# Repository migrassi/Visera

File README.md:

# Visera HX-8K – (HX-8K Visor Hat)
#### Versión 1.0  - Quarantine edition
Extensión I/O para la iCE40HX-8K Breakout Board Evaluation Kit de Lattice 

## Descripción 

La Visera es un accesorio de conexión directa a la placa de entrenamiento en tecnología FPGA “iCE40HX-8K Breakout Board” de Lattice Semiconductors, un modelo basado en la conocida familia FPGA iCE40, de esa marca. La placa se inserta directamente en el único conector de 40 pines que viene poblado de fabrica en la Breakout Board, quedando “en voladizo” hacia afuera, dejando los otros tres conectores de 40 pines, jumpers, LEDs y demás partes de la placa original completamente descubiertos y libres para otras aplicaciones. Esta disposición flotante, sujeta sólo por un lado, es la que le da el nombre de Visera o Visor Hat. 

La Visera fue desarrollada en Mayo de 2020, en el marco de la pandemia mundial del COVID19 y particularmente la cuarentena estricta de la Ciudad de Buenos Aires. Fue resuelta, por lo tanto, con el material del cajón de rezagos del autor, dadas las dificultades  para adquirir componentes nuevos. Esta importante restricción de diseño constituye una de sus fortalezas, ya que prácticamente cualquier aficionado o profesional de la electrónica tendrá disponibles esos mismos componente en su propio cajón, o los podrá adquirir con facilidad en negocios de cercanías.

## Enlaces

Website:https://miguelgrassi.com.ar/visera/

Video de ejemplo. Encoder rotativo, contador en Hexa y decimal, con display de dos dígitos: https://youtu.be/07v77fjeGq4 

Herramienta para generación de caracteres y símbolos personalizados para usar en el display Matriz de Leds: https://editor.p5js.org/migrassi/present/nZ4poi31X

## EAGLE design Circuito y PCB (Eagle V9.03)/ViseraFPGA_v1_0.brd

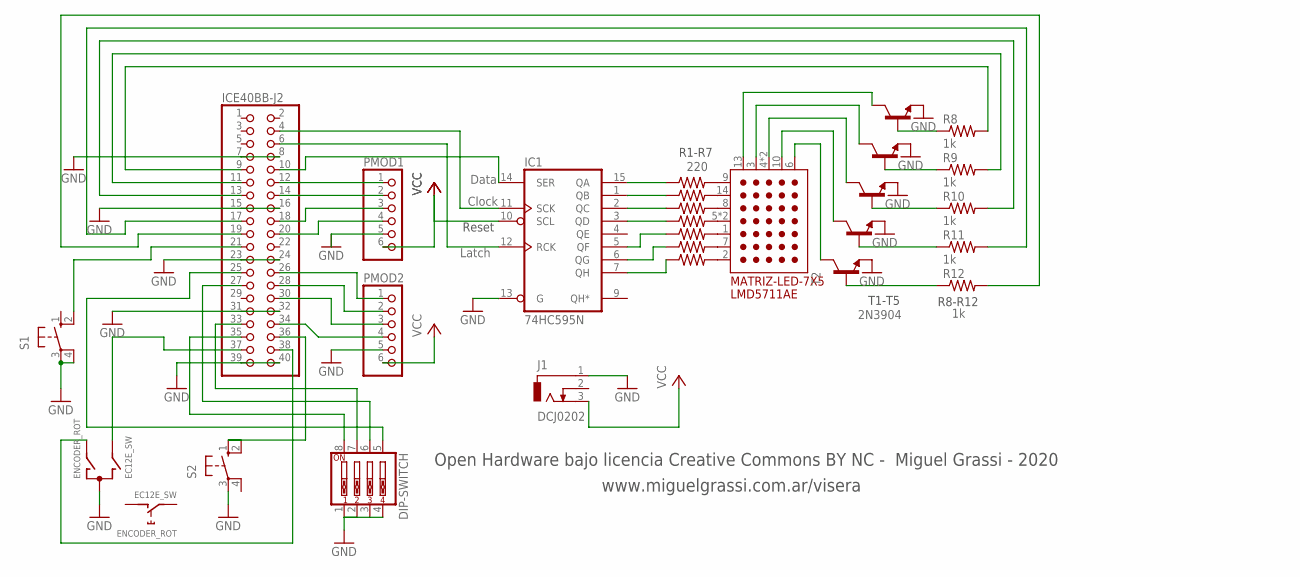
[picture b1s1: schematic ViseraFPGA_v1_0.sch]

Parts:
DIP-SWITCH: SW_DIP-4; EDG-04
ENCODER_ROT: EC12E_SW; ALPS_EC12E_SW
IC1: 74HC595N; DIL16
ICE40BB-J2: PINHD-2X20; 2X20
J1: DCJ0202
MATRIZ-LED-7X5: LMD5711AE
PMOD1, PMOD2: PINHD-1X6; 1X06
R1, R2, R3, R4, R5, R6, R7: 220; 0207/7
R8, R9, R10, R11, R12: 1k; 0207/7
S1, S2: 10-XX; B3F-10XX
T1, T2, T3, T4, T5: 2N3904; TO92

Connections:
GND: DIP-SWITCH.1, DIP-SWITCH.2, DIP-SWITCH.3, DIP-SWITCH.4, ENCODER_ROT.C, IC1.8 (GND), IC1.13 (G), ICE40BB-J2.7, ICE40BB-J2.8, ICE40BB-J2.15, ICE40BB-J2.16, ICE40BB-J2.23, ICE40BB-J2.24, ICE40BB-J2.31, ICE40BB-J2.32, ICE40BB-J2.39, ICE40BB-J2.40, J1.1, PMOD1.5, PMOD2.5, S1.3, S1.4 (P1), S2.3, T1.3 (E), T2.3 (E), T3.3 (E), T4.3 (E), T5.3 (E)
unnamed: MATRIZ-LED-7X5.9 (R1), R1.2
unnamed: MATRIZ-LED-7X5.14 (R2), R2.2
unnamed: MATRIZ-LED-7X5.8 (R3), R3.2
unnamed: MATRIZ-LED-7X5.5 (R4), MATRIZ-LED-7X5.12 (R4), R4.2
unnamed: MATRIZ-LED-7X5.1 (R5), R5.2
unnamed: MATRIZ-LED-7X5.7 (R6), R6.2
unnamed: MATRIZ-LED-7X5.2 (R7), R7.2
unnamed: MATRIZ-LED-7X5.6 (C5), T1.1 (C)
unnamed: MATRIZ-LED-7X5.10 (C4), T2.1 (C)
unnamed: MATRIZ-LED-7X5.4 (C3), MATRIZ-LED-7X5.11 (C3), T3.1 (C)
unnamed: MATRIZ-LED-7X5.3 (C2), T4.1 (C)
unnamed: MATRIZ-LED-7X5.13 (C1), T5.1 (C)
unnamed: R8.1, T5.2 (B)
unnamed: R9.1, T4.2 (B)
unnamed: R10.1, T3.2 (B)
unnamed: R11.1, T2.2 (B)
unnamed: R12.1, T1.2 (B)
unnamed: IC1.15 (QA), R1.1
unnamed: ICE40BB-J2.9, R8.2
unnamed: IC1.2 (QC), R3.1
unnamed: IC1.1 (QB), R2.1
unnamed: ICE40BB-J2.11, R9.2
unnamed: ICE40BB-J2.13, R10.2
unnamed: ICE40BB-J2.17, R11.2
unnamed: ICE40BB-J2.19, R12.2
unnamed: IC1.7 (QH), R7.1
unnamed: IC1.6 (QG), R6.1
unnamed: IC1.5 (QF), R5.1
unnamed: ICE40BB-J2.21, S1.2 (S1)
unnamed: ICE40BB-J2.36, S2.1 (S), S2.2 (S1)
unnamed: DIP-SWITCH.5, ICE40BB-J2.25
unnamed: DIP-SWITCH.6, ICE40BB-J2.27
unnamed: DIP-SWITCH.7, ICE40BB-J2.33
unnamed: DIP-SWITCH.8, ICE40BB-J2.35
unnamed: ENCODER_ROT.B, ICE40BB-J2.37
unnamed: ENCODER_ROT.A, ICE40BB-J2.38
unnamed: ICE40BB-J2.12, PMOD1.1
unnamed: IC1.11 (SCK), ICE40BB-J2.4
unnamed: IC1.12 (RCK), ICE40BB-J2.6
unnamed: IC1.14 (SER), ICE40BB-J2.10
unnamed: IC1.3 (QD), R4.1
unnamed: ICE40BB-J2.14, PMOD1.2
unnamed: ICE40BB-J2.18, PMOD1.3
unnamed: ICE40BB-J2.20, PMOD1.4
unnamed: ICE40BB-J2.26, PMOD2.1
unnamed: ICE40BB-J2.28, PMOD2.2
unnamed: ICE40BB-J2.30, PMOD2.3
unnamed: ICE40BB-J2.34, PMOD2.4
VCC: IC1.10 (SCL), IC1.16 (VCC), J1.3, PMOD1.6, PMOD2.6

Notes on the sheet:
Data
Clock
Latch
Reset
R1-R7
T1-T5
R8-R12
Open Hardware bajo licencia Creative Commons BY NC - Miguel Grassi - 2020
www.miguelgrassi.com.ar/visera

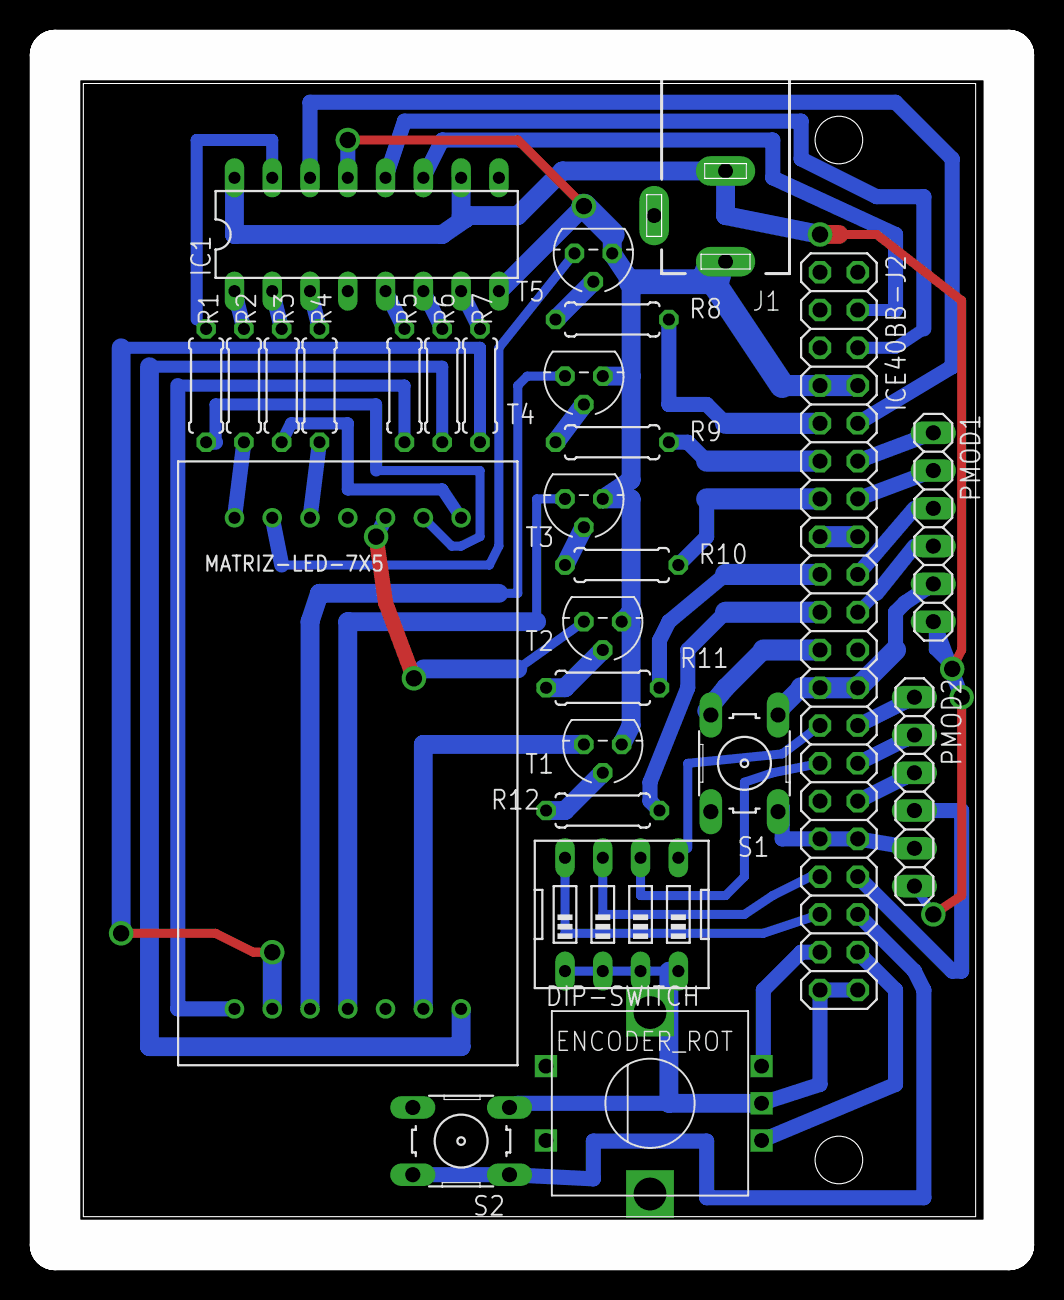
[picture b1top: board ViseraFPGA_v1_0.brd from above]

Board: 2 copper layers, 64.1 x 80.0 mm, 27 parts (0 on the bottom side), 50 nets.

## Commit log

2020-06-26 Hard y Soft para Visera
    Creación de archivos de Circuitos, PCB y Modelos 3D para el hardware, bloques y ejemplos para el software
2020-06-26 Commit inicial
    Creación de archivos de Circuitos, PCB y Modelos 3D para el hardware, bloques y ejemplos para el software
